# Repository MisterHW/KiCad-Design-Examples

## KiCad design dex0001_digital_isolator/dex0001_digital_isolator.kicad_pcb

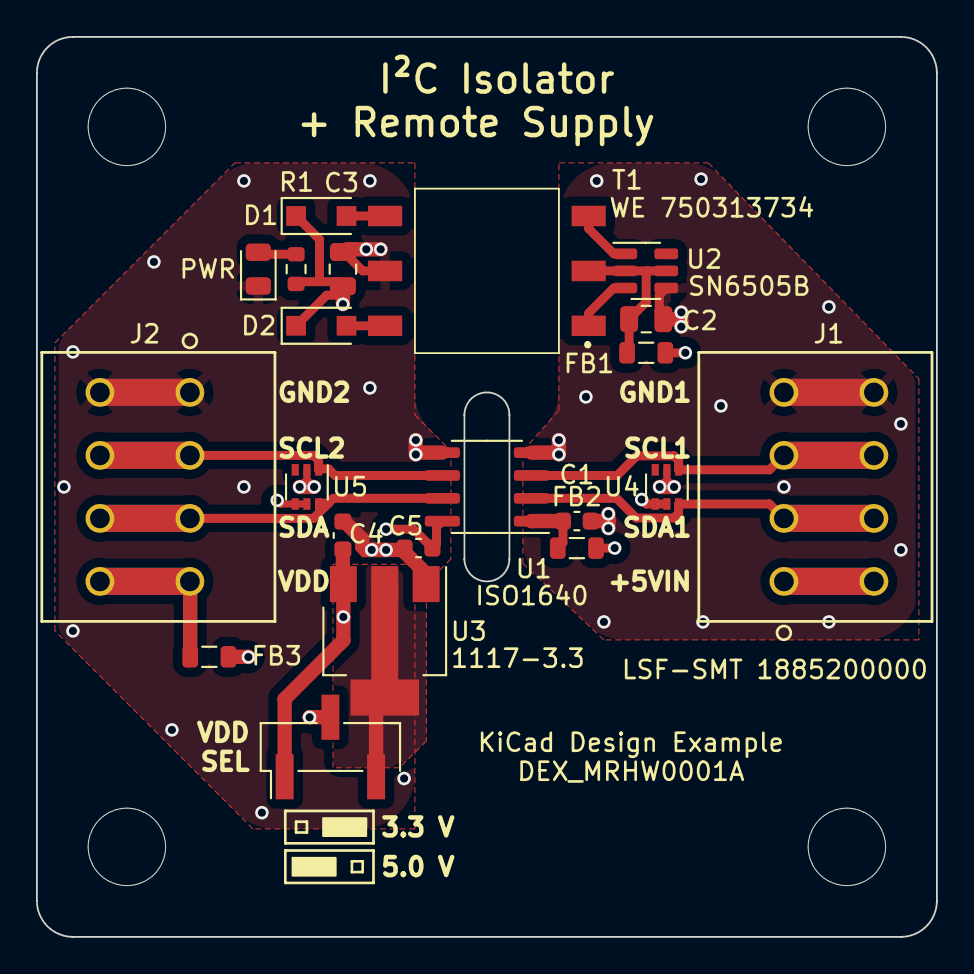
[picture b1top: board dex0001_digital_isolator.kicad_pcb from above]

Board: 4 copper layers, 50.0 x 50.0 mm, 26 parts (0 on the bottom side), 18 nets.

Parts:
C1, C4, C5: 100nF; C_0603_1608Metric
C2, C3: 10uF; C_0805_2012Metric
D1, D2: PMEG4010EH; D_SOD-123F
FB1, FB2, FB3: FB; L_0805_2012Metric
H1, H2, H3, H4: M4 NPTH; MountingHole_4.3mm_M4_ISO14580
J1, J2: LSF-SMT 1885200000; 1885200000
JP1: Jumper_3_Bridged12; PinHeader_1x03_P2.54mm_Vertical_SMD_Pin1Left
JS1: Jumper_Shunt; Jumper_Shunt_2.54mm
LED1: AMB; LED_0805_2012Metric
R1: 2.2k; R_0603_1608Metric
T1: WE 750313734; WE_MID_PPTI_8.0x9.1x7.6
U1: ISO1640; SOIC-8_3.9x4.9mm_P1.27mm
U2: SN6505B; SOT-23-6
U3: 1117-3.3; SOT-223-3_TabPin2
U4, U5: NUP2202; SOT-363_SC-70-6

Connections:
/SCL1: J1.5, J1.6, U1.3 (SCL1), U4.1
/SCL2: J2.3, J2.4, U1.6 (SCL2), U5.1
/SDA1: J1.3, J1.4, U1.2 (SDA1), U4.6
/SDA2: J2.5, J2.6, U1.7 (SDA2), U5.6
GND1: C1.2, C2.1, J1.7, J1.8, U1.4 (GND1), U2.4 (GND), U4.2
GND2: C3.1, C4.1, C5.1, J2.1, J2.2, LED1.1 (K), T1.5, U1.5 (GND2), U3.1 (GND), U5.2
unnamed: C1.1, FB2.1, U1.1 (VCC1)
unnamed: C2.2, FB1.1, T1.2, U2.2 (VCC), U2.5 (EN)
unnamed: C3.2, C4.2, D1.1 (K), D2.1 (K), JP1.1 (A), R1.1, U3.3 (VI)
unnamed: C5.2, FB3.2, JP1.2 (C), U1.8 (VCC2), U5.4, U5.5
unnamed: D1.2 (A), T1.4
unnamed: D2.2 (A), T1.6
unnamed: FB1.2, FB2.2, J1.1, J1.2, U4.4, U4.5
unnamed: FB3.1, J2.7, J2.8
unnamed: JP1.3 (B), U3.2 (VO)
unnamed: LED1.2 (A), R1.2
unnamed: T1.1, U2.3 (D2)
unnamed: T1.3, U2.1 (D1)

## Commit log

2020-11-22 different clearance for board edge vs slots
    dex0001 illustrates localized clearances to Edge.Cuts by enclosing slot contours in rule areas as opposed to the bare board outline. Conversely, the board outline can be copied to Margin and treated 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
